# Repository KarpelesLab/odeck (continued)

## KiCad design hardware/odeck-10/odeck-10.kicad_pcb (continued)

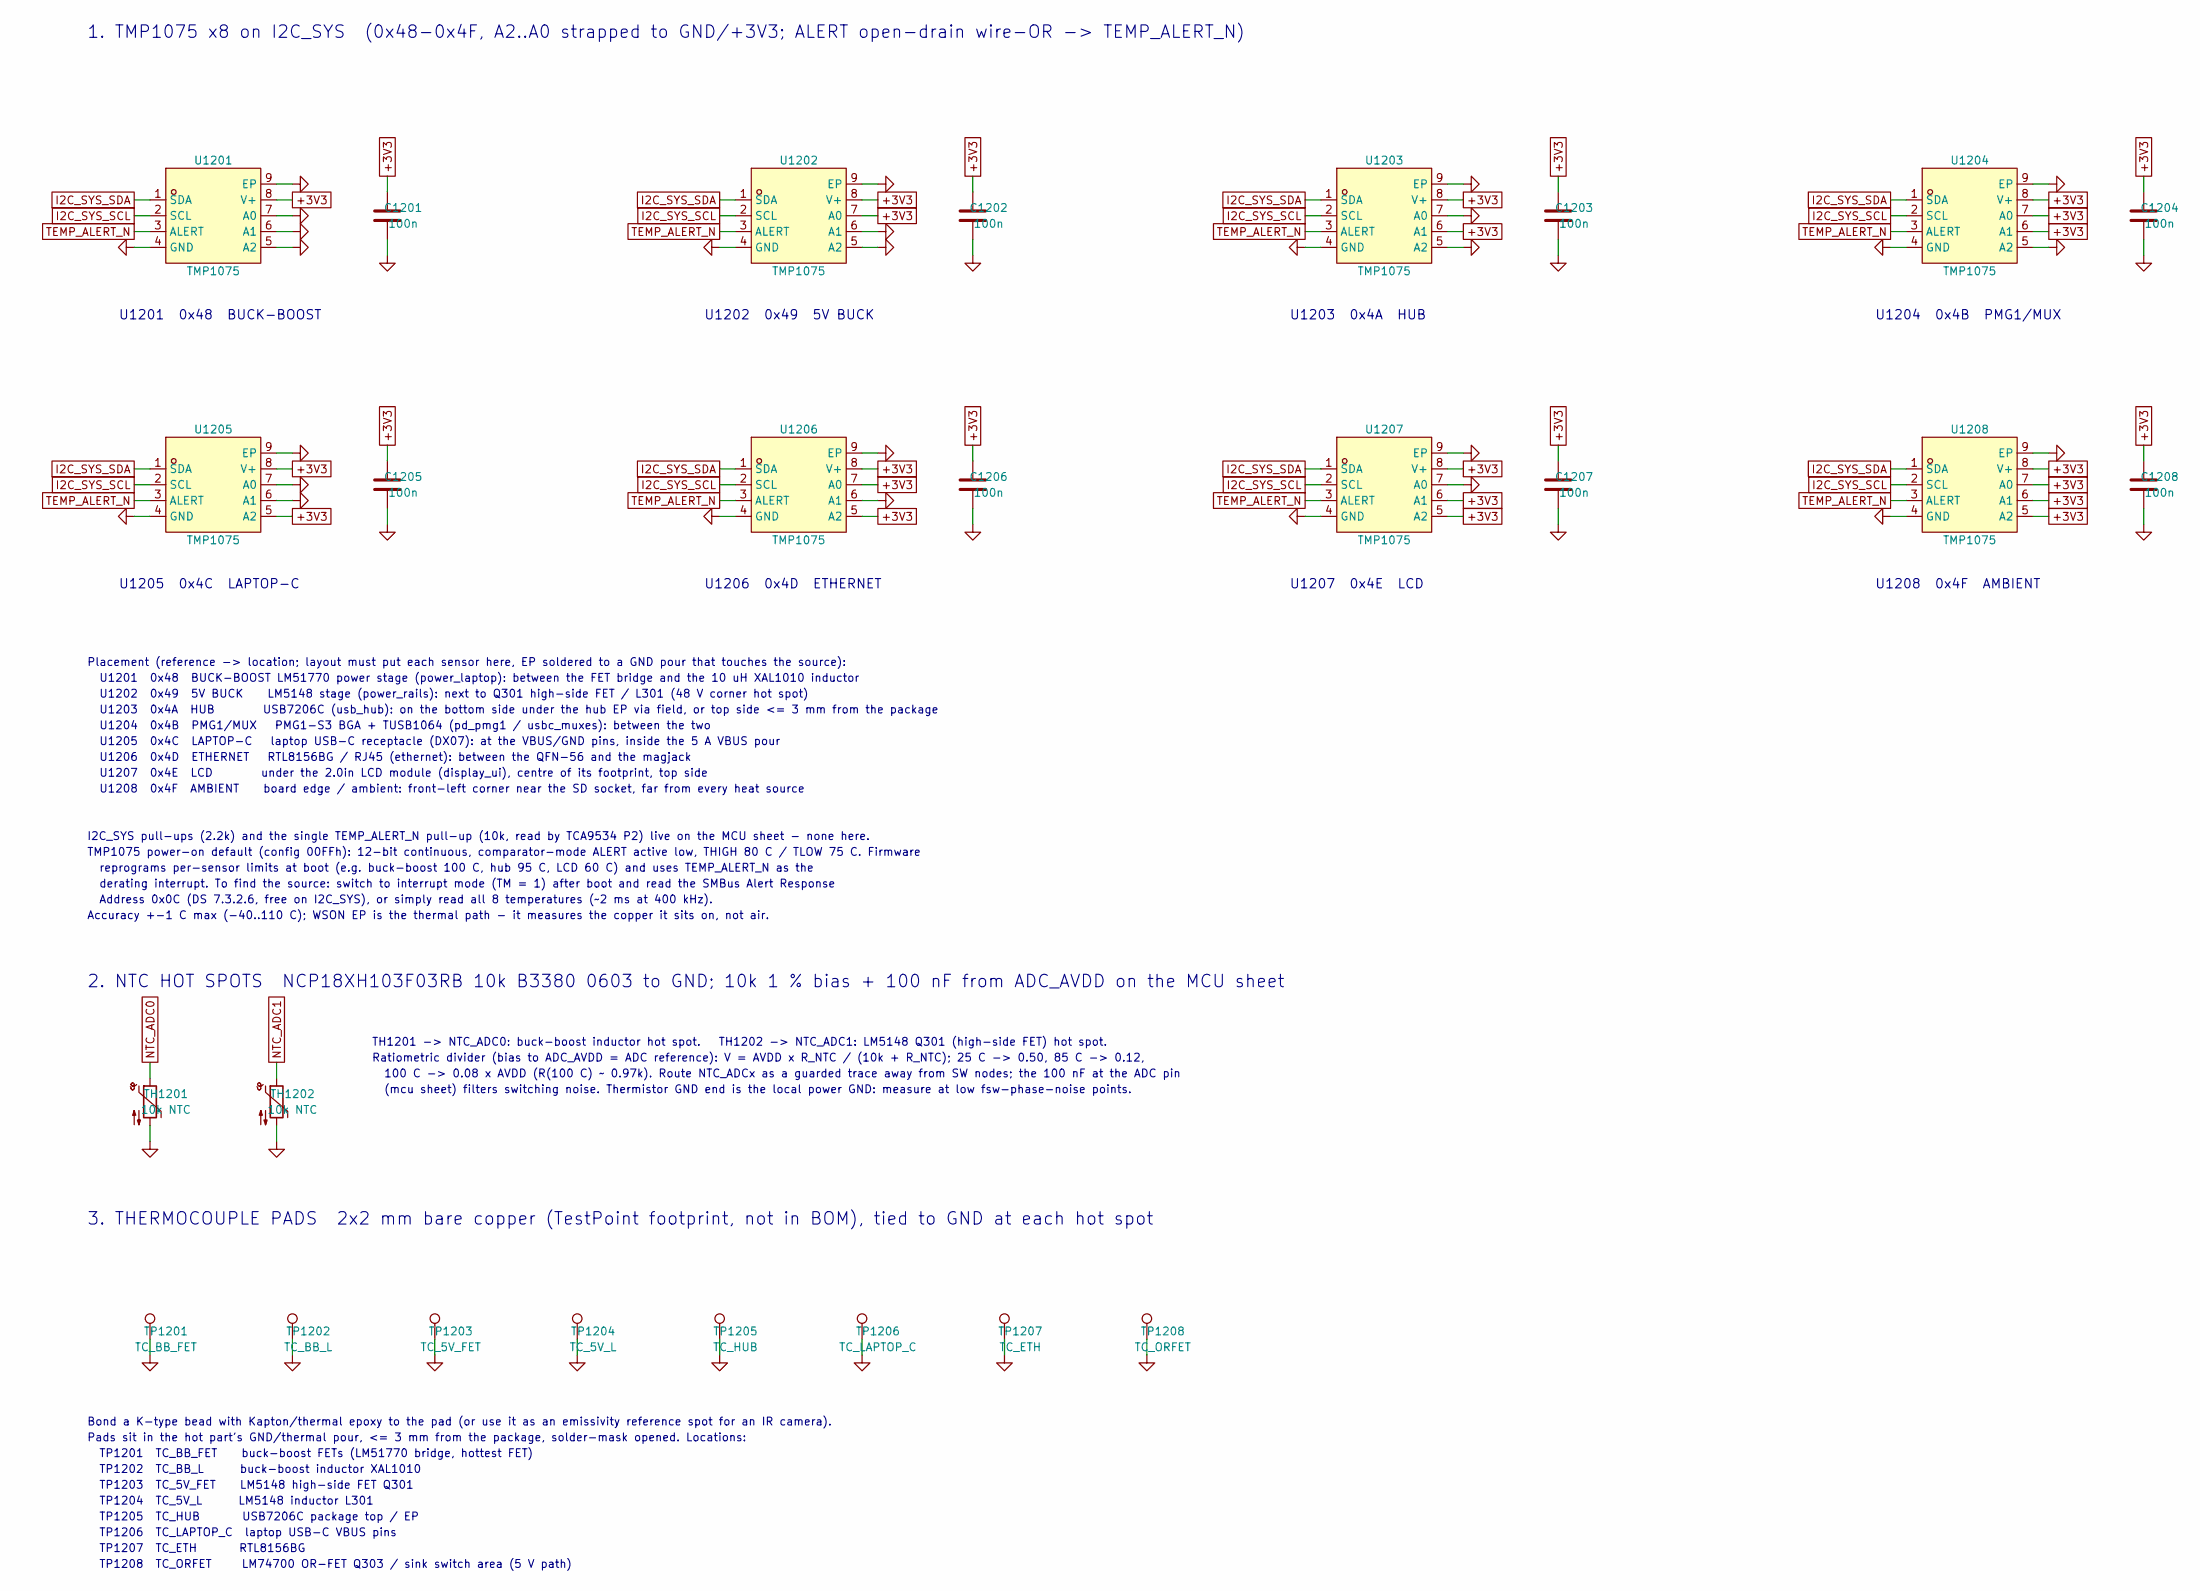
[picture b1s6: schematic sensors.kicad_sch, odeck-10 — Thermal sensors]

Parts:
C1201, C1202, C1203, C1204, C1205, C1206, C1207, C1208: 100n; C_0402_1005Metric; LCSC C1525
TH1201, TH1202: 10k NTC; R_0603_1608Metric; LCSC C13564
TP1201: TC_BB_FET; TestPoint_Pad_2.0x2.0mm
TP1202: TC_BB_L; TestPoint_Pad_2.0x2.0mm
TP1203: TC_5V_FET; TestPoint_Pad_2.0x2.0mm
TP1204: TC_5V_L; TestPoint_Pad_2.0x2.0mm
TP1205: TC_HUB; TestPoint_Pad_2.0x2.0mm
TP1206: TC_LAPTOP_C; TestPoint_Pad_2.0x2.0mm
TP1207: TC_ETH; TestPoint_Pad_2.0x2.0mm
TP1208: TC_ORFET; TestPoint_Pad_2.0x2.0mm
U1201, U1202, U1203, U1204, U1205, U1206, U1207, U1208: TMP1075; WSON-8_L2.0-W2.0-P0.50-TL-EP; MPN TMP1075DSGR; LCSC C2870250

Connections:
+3V3: C1201.1, C1202.1, C1203.1, C1204.1, C1205.1, C1206.1, C1207.1, C1208.1, U1201.8 (V+), U1202.7 (A0), U1202.8 (V+), U1203.6 (A1), U1203.8 (V+), U1204.6 (A1), U1204.7 (A0), U1204.8 (V+), U1205.5 (A2), U1205.8 (V+), U1206.5 (A2), U1206.7 (A0), U1206.8 (V+), U1207.5 (A2), U1207.6 (A1), U1207.8 (V+), U1208.5 (A2), U1208.6 (A1), U1208.7 (A0), U1208.8 (V+); also elsewhere on the board
GND: C1201.2, C1202.2, C1203.2, C1204.2, C1205.2, C1206.2, C1207.2, C1208.2, TH1201.2, TH1202.2, TP1201.1, TP1202.1, TP1203.1, TP1204.1, TP1205.1, TP1206.1, TP1207.1, TP1208.1, U1201.4 (GND), U1201.5 (A2), U1201.6 (A1), U1201.7 (A0), U1201.9 (EP), U1202.4 (GND), U1202.5 (A2), U1202.6 (A1), U1202.9 (EP), U1203.4 (GND), U1203.5 (A2), U1203.7 (A0), U1203.9 (EP), U1204.4 (GND), U1204.5 (A2), U1204.9 (EP), U1205.4 (GND), U1205.6 (A1), U1205.7 (A0), U1205.9 (EP), U1206.4 (GND), U1206.6 (A1), U1206.9 (EP), U1207.4 (GND), U1207.7 (A0), U1207.9 (EP), U1208.4 (GND), U1208.9 (EP); also elsewhere on the board
I2C_SYS_SCL: U1201.2 (SCL), U1202.2 (SCL), U1203.2 (SCL), U1204.2 (SCL), U1205.2 (SCL), U1206.2 (SCL), U1207.2 (SCL), U1208.2 (SCL); also elsewhere on the board
I2C_SYS_SDA: U1201.1 (SDA), U1202.1 (SDA), U1203.1 (SDA), U1204.1 (SDA), U1205.1 (SDA), U1206.1 (SDA), U1207.1 (SDA), U1208.1 (SDA); also elsewhere on the board
NTC_ADC0: TH1201.1; also elsewhere on the board
NTC_ADC1: TH1202.1; also elsewhere on the board
TEMP_ALERT_N: U1201.3 (ALERT), U1202.3 (ALERT), U1203.3 (ALERT), U1204.3 (ALERT), U1205.3 (ALERT), U1206.3 (ALERT), U1207.3 (ALERT), U1208.3 (ALERT); also elsewhere on the board

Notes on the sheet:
1. TMP1075 x8 on I2C_SYS (0x48-0x4F, A2..A0 strapped to GND/+3V3; ALERT open-drain wire-OR -> TEMP_ALERT_N)
U1201 0x48 BUCK-BOOST
U1202 0x49 5V BUCK
U1203 0x4A HUB
U1204 0x4B PMG1/MUX
U1205 0x4C LAPTOP-C
U1206 0x4D ETHERNET
U1207 0x4E LCD
U1208 0x4F AMBIENT
Placement (reference -> location; layout must put each sensor here, EP soldered to a GND pour that touches the source):
U1201 0x48 BUCK-BOOST LM51770 power stage (power_laptop): between the FET bridge and the 10 uH XAL1010 inductor
U1202 0x49 5V BUCK LM5148 stage (power_rails): next to Q301 high-side FET / L301 (48 V corner hot spot)
U1203 0x4A HUB USB7206C (usb_hub): on the bottom side under the hub EP via field, or top side <= 3 mm from the package
U1204 0x4B PMG1/MUX PMG1-S3 BGA + TUSB1064 (pd_pmg1 / usbc_muxes): between the two
U1205 0x4C LAPTOP-C laptop USB-C receptacle (DX07): at the VBUS/GND pins, inside the 5 A VBUS pour
U1206 0x4D ETHERNET RTL8156BG / RJ45 (ethernet): between the QFN-56 and the magjack
U1207 0x4E LCD under the 2.0in LCD module (display_ui), centre of its footprint, top side
U1208 0x4F AMBIENT board edge / ambient: front-left corner near the SD socket, far from every heat source
I2C_SYS pull-ups (2.2k) and the single TEMP_ALERT_N pull-up (10k, read by TCA9534 P2) live on the MCU sheet - none here.
TMP1075 power-on default (config 00FFh): 12-bit continuous, comparator-mode ALERT active low, THIGH 80 C / TLOW 75 C. Firmware
reprograms per-sensor limits at boot (e.g. buck-boost 100 C, hub 95 C, LCD 60 C) and uses TEMP_ALERT_N as the
derating interrupt. To find the source: switch to interrupt mode (TM = 1) after boot and read the SMBus Alert Response
Address 0x0C (DS 7.3.2.6, free on I2C_SYS), or simply read all 8 temperatures (~2 ms at 400 kHz).
Accuracy +-1 C max (-40..110 C); WSON EP is the thermal path - it measures the copper it sits on, not air.
2. NTC HOT SPOTS NCP18XH103F03RB 10k B3380 0603 to GND; 10k 1 % bias + 100 nF from ADC_AVDD on the MCU sheet
TH1201 -> NTC_ADC0: buck-boost inductor hot spot. TH1202 -> NTC_ADC1: LM5148 Q301 (high-side FET) hot spot.
Ratiometric divider (bias to ADC_AVDD = ADC reference): V = AVDD x R_NTC / (10k + R_NTC); 25 C -> 0.50, 85 C -> 0.12,
100 C -> 0.08 x AVDD (R(100 C) ~ 0.97k). Route NTC_ADCx as a guarded trace away from SW nodes; the 100 nF at the ADC pin
(mcu sheet) filters switching noise. Thermistor GND end is the local power GND: measure at low fsw-phase-noise points.
3. THERMOCOUPLE PADS 2x2 mm bare copper (TestPoint footprint, not in BOM), tied to GND at each hot spot
Bond a K-type bead with Kapton/thermal epoxy to the pad (or use it as an emissivity reference spot for an IR camera).
Pads sit in the hot part's GND/thermal pour, <= 3 mm from the package, solder-mask opened. Locations:
TP1201 TC_BB_FET buck-boost FETs (LM51770 bridge, hottest FET)
TP1202 TC_BB_L buck-boost inductor XAL1010
TP1203 TC_5V_FET LM5148 high-side FET Q301
TP1204 TC_5V_L LM5148 inductor L301
TP1205 TC_HUB USB7206C package top / EP
TP1206 TC_LAPTOP_C laptop USB-C VBUS pins
TP1207 TC_ETH RTL8156BG
TP1208 TC_ORFET LM74700 OR-FET Q303 / sink switch area (5 V path)

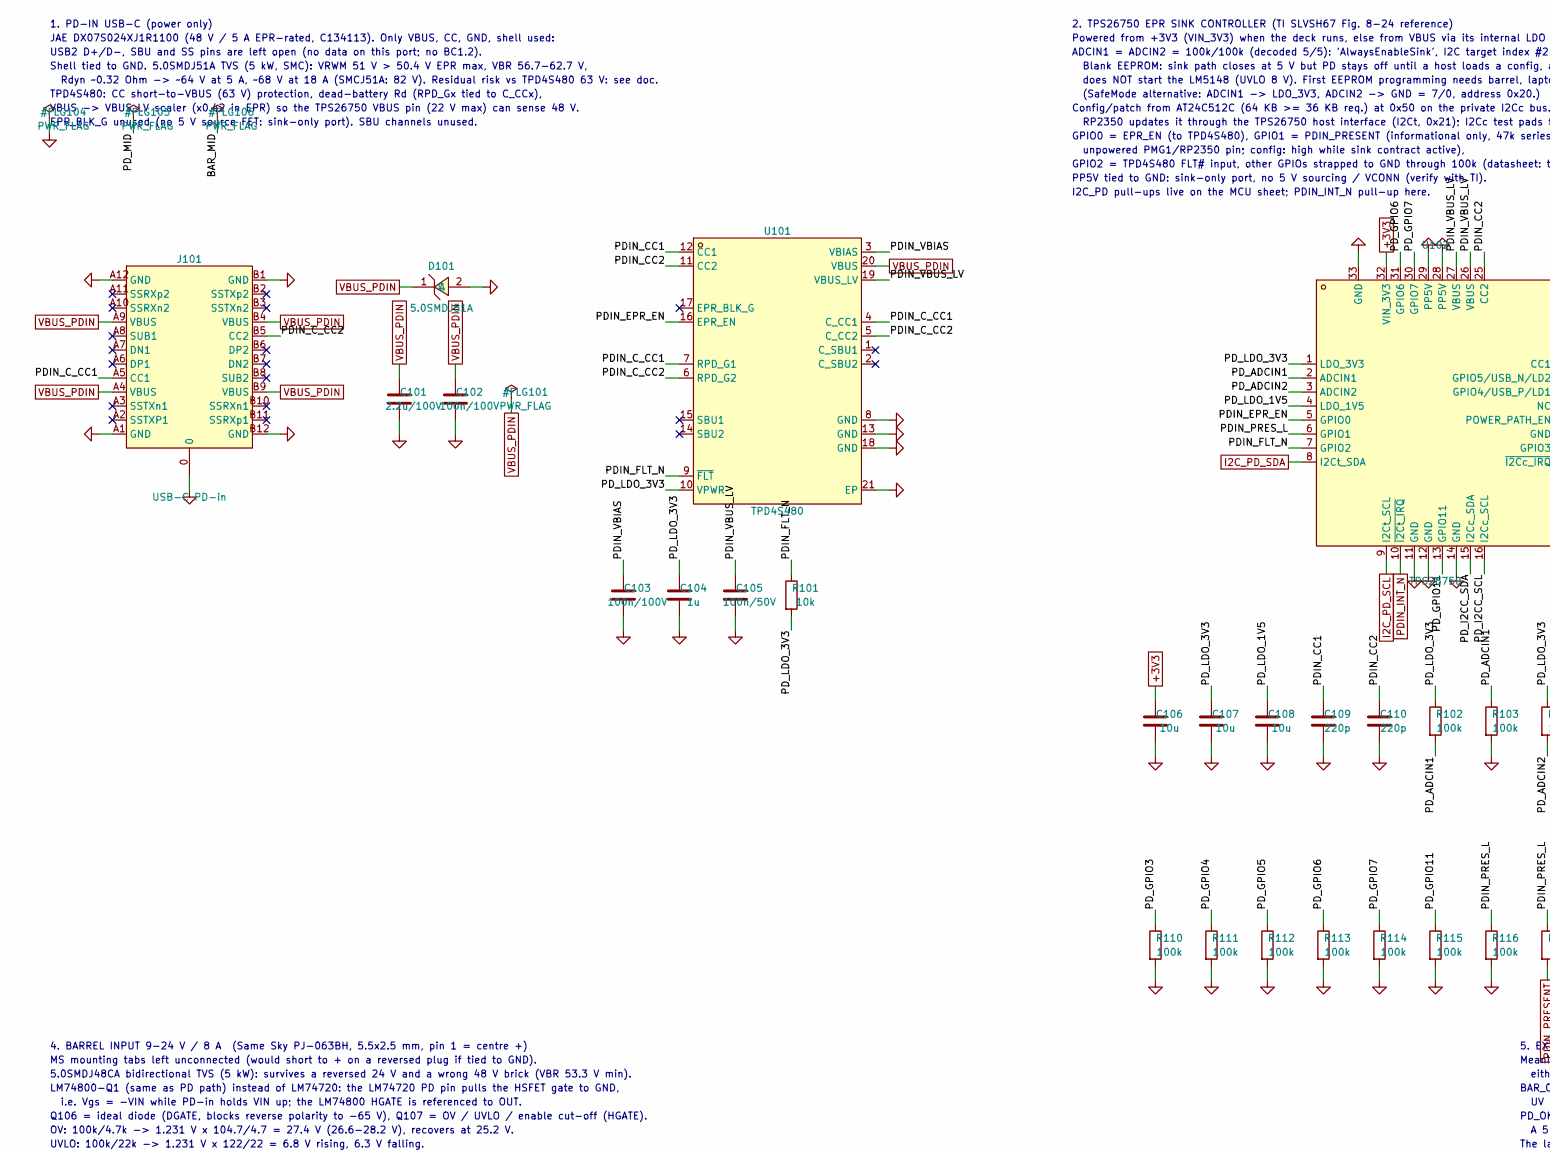
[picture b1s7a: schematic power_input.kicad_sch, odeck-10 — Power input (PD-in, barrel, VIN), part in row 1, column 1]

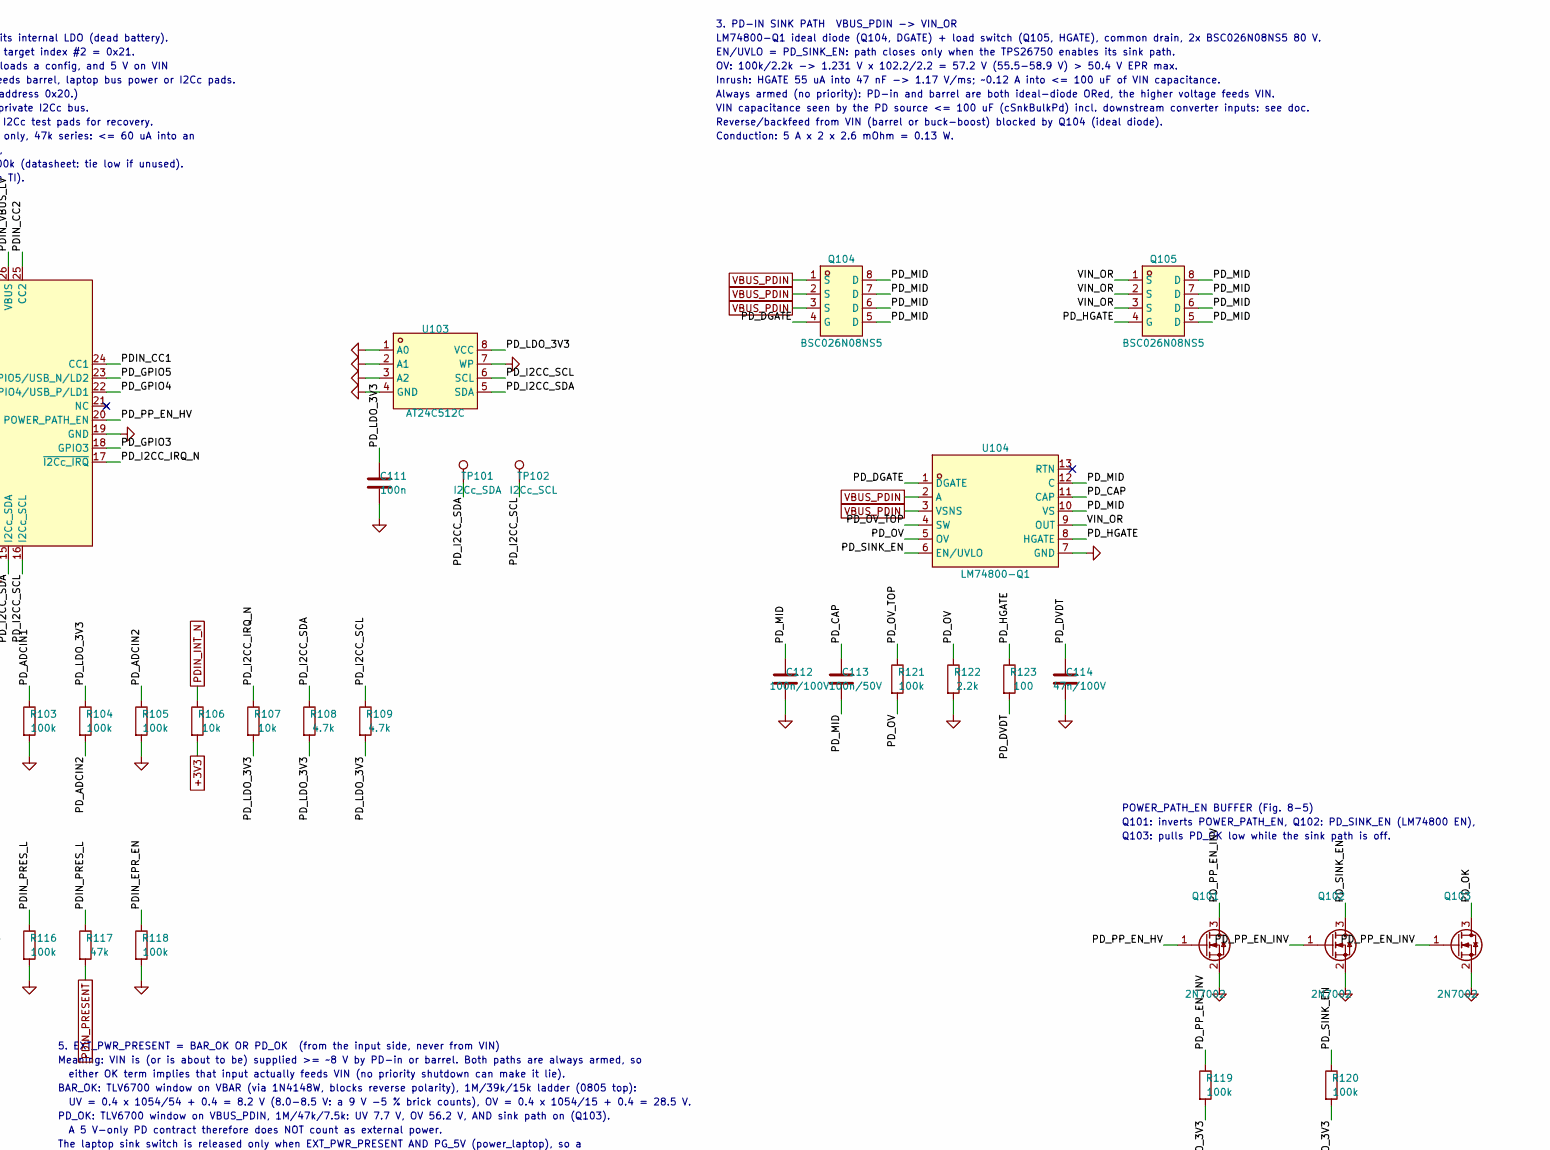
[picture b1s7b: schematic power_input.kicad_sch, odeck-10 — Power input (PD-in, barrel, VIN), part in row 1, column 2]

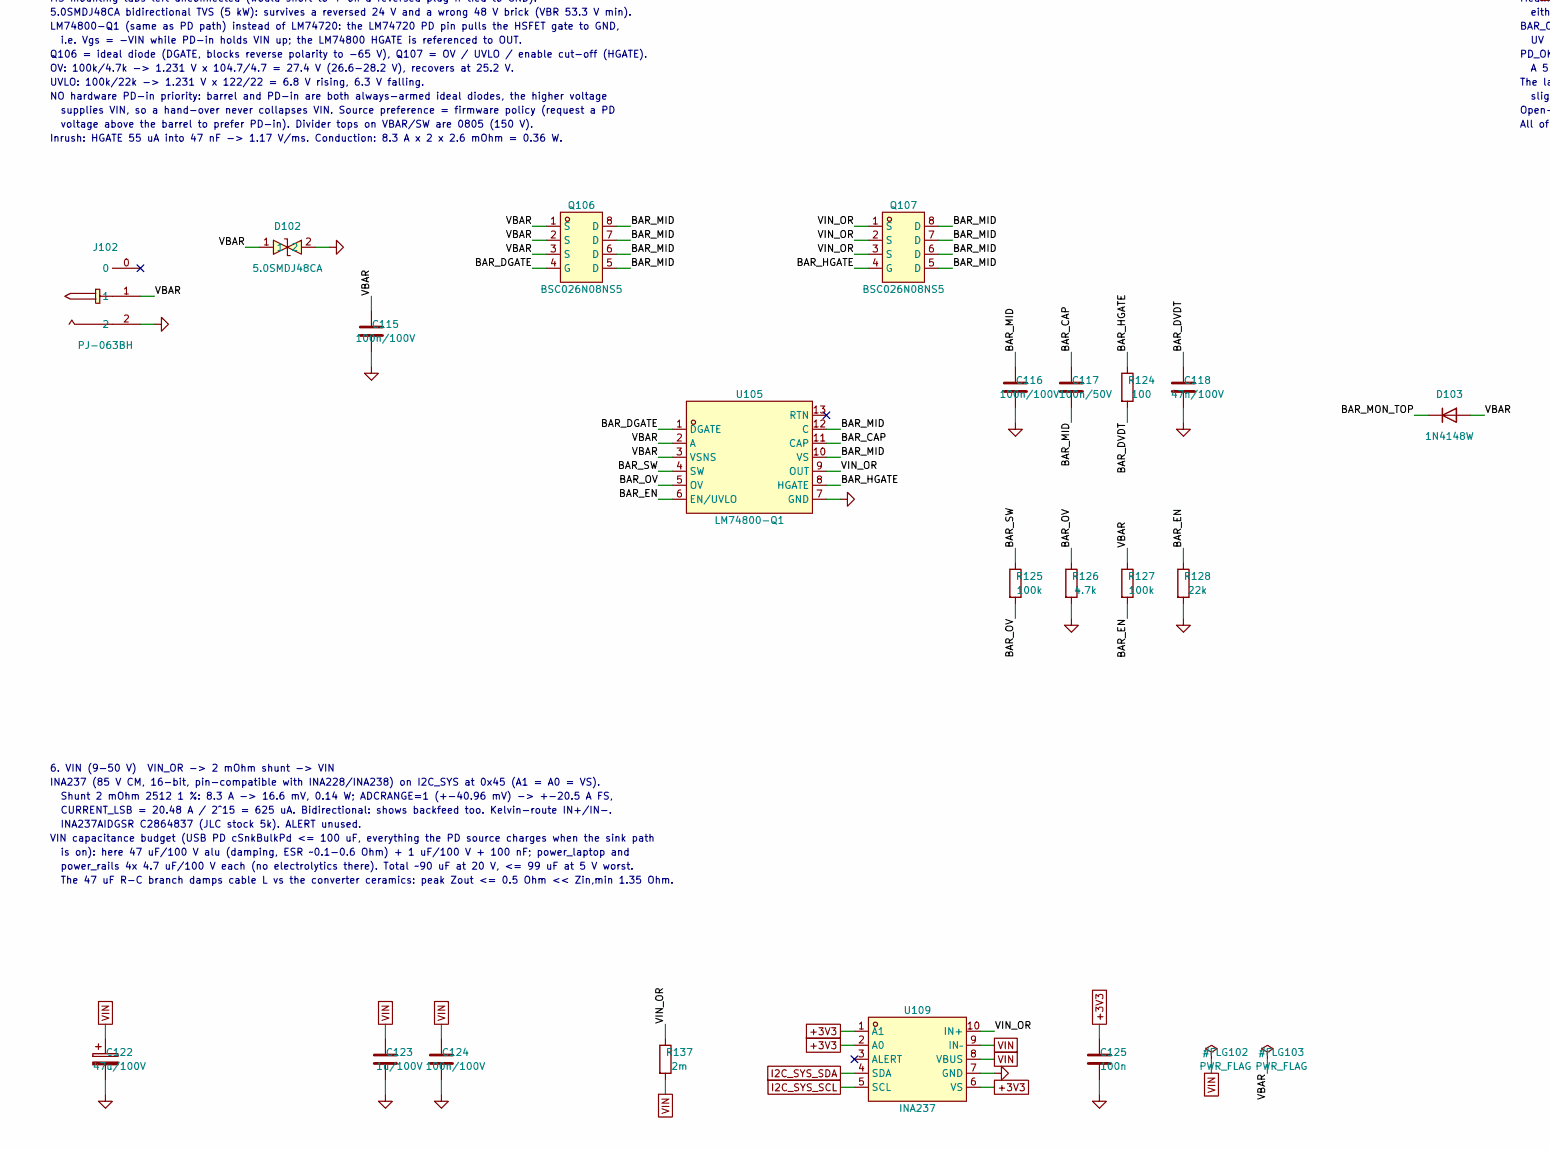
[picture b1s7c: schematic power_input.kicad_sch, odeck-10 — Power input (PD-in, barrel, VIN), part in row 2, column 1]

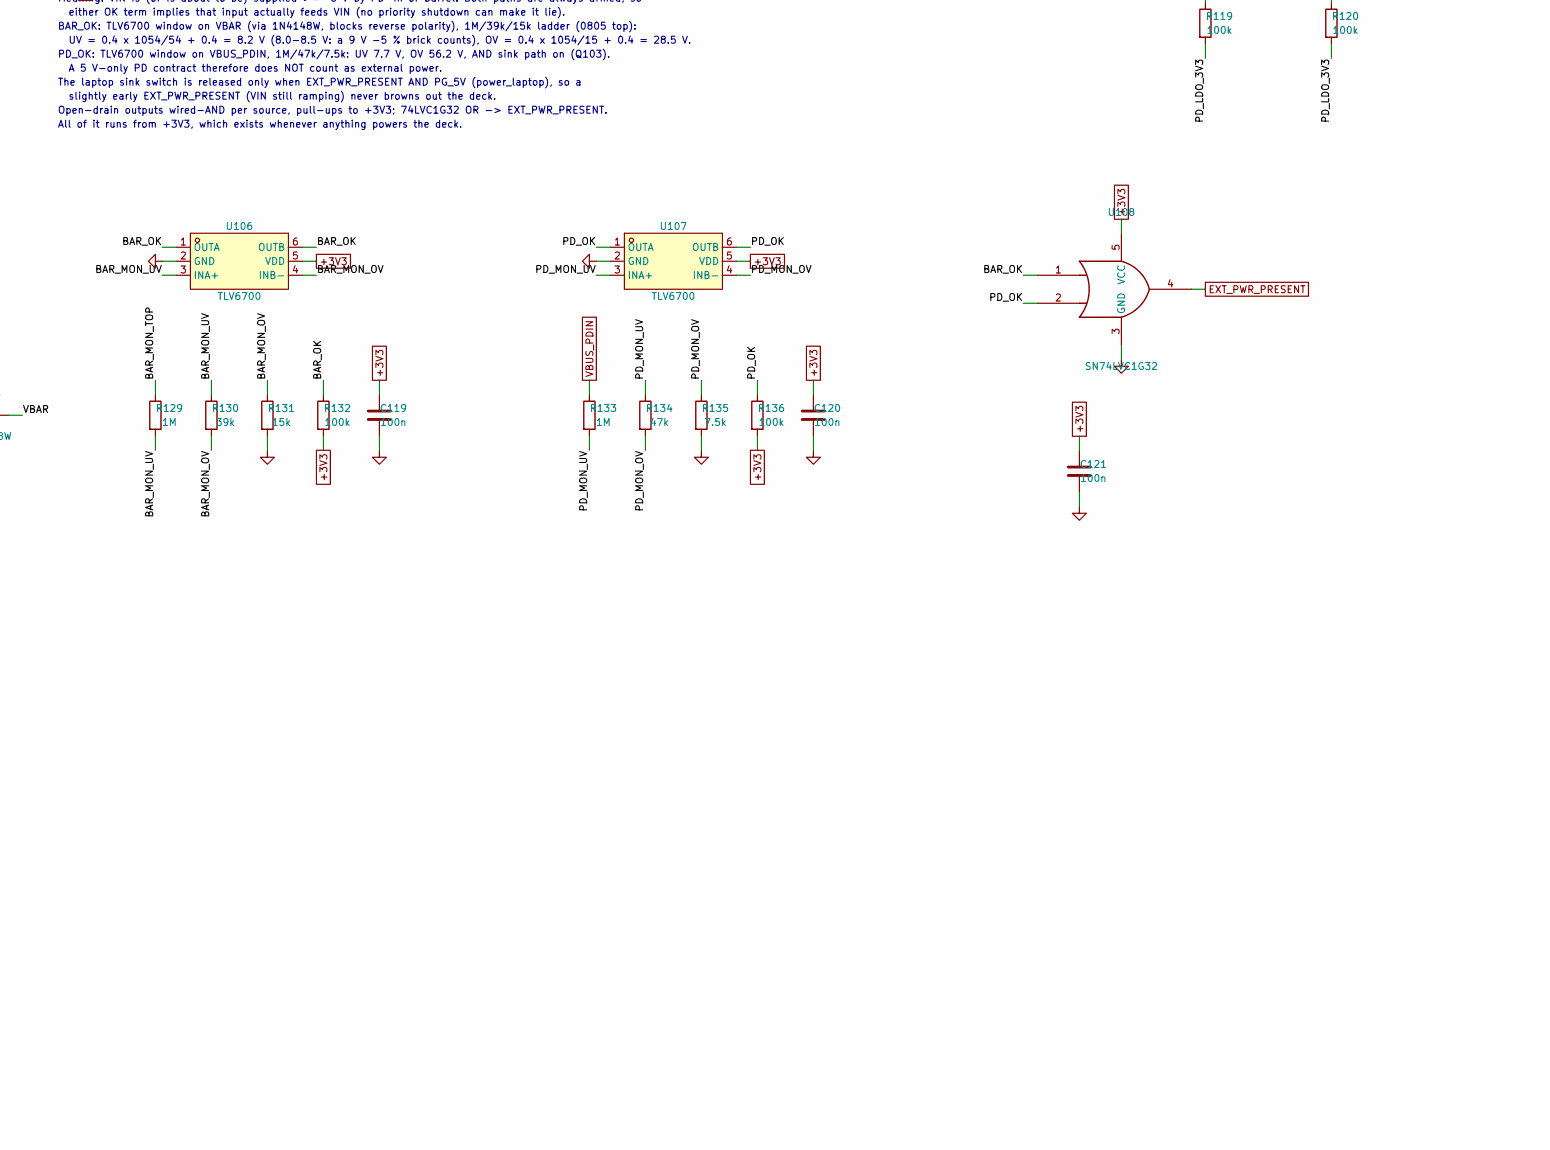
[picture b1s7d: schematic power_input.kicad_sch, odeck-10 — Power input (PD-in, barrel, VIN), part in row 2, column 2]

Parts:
C101: 2.2u/100V; C_1210_3225Metric; LCSC C153036
C102, C103, C112, C115, C116, C124: 100n/100V; C_0805_2012Metric; LCSC C28233
C104: 1u; C_0402_1005Metric; LCSC C52923
C105, C113, C117: 100n/50V; C_0603_1608Metric; LCSC C14663
C106, C107, C108: 10u; C_0603_1608Metric; LCSC C19702
C109, C110: 220p; C_0603_1608Metric; LCSC C1603
C111, C119, C120, C121, C125: 100n; C_0402_1005Metric; LCSC C1525
C114, C118: 47n/100V; C_0603_1608Metric; LCSC C576852
C122: 47u/100V; CP_Elec_10x10; LCSC C371305
C123: 1u/100V; C_0805_2012Metric; LCSC C126585
D101: 5.0SMDJ51A; SMC_L6.9-W5.9-LS7.9-RD; MPN 5.0SMDJ51A; LCSC C2990373
D102: 5.0SMDJ48CA; SMC_L6.9-W5.9-LS7.9-BI; MPN 5.0SMDJ48CA; LCSC C2649886
D103: 1N4148W; D_SOD-123; LCSC C81598
J101: USB-C PD-in; USB-C-TH_DX07S024XJ1R1100-1; MPN DX07S024XJ1R1100; LCSC C134113
J102: PJ-063BH; DC-IN_PJ-063BH; MPN PJ-063BH; LCSC C3095900
Q101, Q102, Q103: 2N7002; SOT-23; LCSC C8545
Q104, Q105, Q106, Q107: BSC026N08NS5; PG-TDSON-8_L5.0-W6.0-P1.27-BL-EP; MPN BSC026N08NS5ATMA1; LCSC C5955453
R101, R106, R107: 10k; R_0402_1005Metric; LCSC C25744
R102, R103, R104, R105, R110, R111, R112, R113, R114, R115, R116, R118, R119, R120, R132, R136: 100k; R_0402_1005Metric; LCSC C25741
R108, R109, R126: 4.7k; R_0402_1005Metric; LCSC C25900
R117, R134: 47k; R_0402_1005Metric; LCSC C25792
R121, R125, R127: 100k; R_0805_2012Metric; LCSC C149504
R122: 2.2k; R_0402_1005Metric; LCSC C25879
R123, R124: 100; R_0402_1005Metric; LCSC C25076
R128: 22k; R_0402_1005Metric; LCSC C25768
R129, R133: 1M; R_0805_2012Metric; LCSC C17514
R130: 39k; R_0603_1608Metric; LCSC C23153
R131: 15k; R_0402_1005Metric; LCSC C25756
R135: 7.5k; R_0603_1608Metric; LCSC C23234
R137: 2m; R_2512_6332Metric; MPN RLP25FEGR002; LCSC C459679
TP101: I2Cc_SDA; TestPoint_Pad_D1.0mm
TP102: I2Cc_SCL; TestPoint_Pad_D1.0mm
U101: TPD4S480; WQFN-20_L3.0-W3.0-P0.40-BL-EP1.7; MPN TPD4S480RUKR; LCSC C43131250
U102: TPS26750; QFN-32_L4.0-W4.0-P0.40-BL-EP2.8; MPN TPS26750SRSMR; LCSC C42166327
U103: AT24C512C; SOIC-8_L4.9-W3.9-P1.27-LS6.0-BL; MPN AT24C512C-SSHD-T; LCSC C12371
U104, U105: LM74800-Q1; WSON-12_L3.0-W3.0-P0.50-TL-EP-2; MPN LM74800QDRRRQ1; LCSC C3215600
U106, U107: TLV6700; TSOT-23-6_L2.9-W1.6-P0.95-LS2.8-BR; MPN TLV6700DDCR; LCSC C2868382
U108: SN74LVC1G32; SOT-23-5; LCSC C10096
U109: INA237; VSSOP-10_L3.0-W3.0-P0.50-LS4.9-BL; MPN INA237AIDGSR; LCSC C2864837

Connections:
+3V3: C106.1, C119.1, C120.1, C121.1, C125.1, R106.2, R132.2, R136.2, U102.32 (VIN_3V3), U106.5 (VDD), U107.5 (VDD), U108.5 (VCC), U109.1 (A1), U109.2 (A0), U109.6 (VS); also elsewhere on the board
/Power input/BAR_CAP: C117.1, U105.11 (CAP)
/Power input/BAR_DGATE: Q106.4 (G), U105.1 (DGATE)
/Power input/BAR_DVDT: C118.1, R124.2
/Power input/BAR_EN: R127.2, R128.1, U105.6 (EN/UVLO)
/Power input/BAR_HGATE: Q107.4 (G), R124.1, U105.8 (HGATE)
/Power input/BAR_MID: C116.1, C117.2, Q106.5 (D), Q106.6 (D), Q106.7 (D), Q106.8 (D), Q107.5 (D), Q107.6 (D), Q107.7 (D), Q107.8 (D), U105.10 (VS), U105.12 (C)
/Power input/BAR_MON_OV: R130.2, R131.1, U106.4 (INB-)
/Power input/BAR_MON_TOP: D103.1 (K), R129.1
/Power input/BAR_MON_UV: R129.2, R130.1, U106.3 (INA+)
/Power input/BAR_OK: R132.1, U106.1 (OUTA), U106.6 (OUTB), U108.1
/Power input/BAR_OV: R125.2, R126.1, U105.5 (OV)
/Power input/BAR_SW: R125.1, U105.4 (SW)
/Power input/PDIN_CC1: C109.1, U101.12 (CC1), U102.24 (CC1)
/Power input/PDIN_CC2: C110.1, U101.11 (CC2), U102.25 (CC2)
/Power input/PDIN_C_CC1: J101.A5 (CC1), U101.4 (C_CC1), U101.7 (RPD_G1)
/Power input/PDIN_C_CC2: J101.B5 (CC2), U101.5 (C_CC2), U101.6 (RPD_G2)
/Power input/PDIN_EPR_EN: R118.1, U101.16 (EPR_EN), U102.5 (GPIO0)
/Power input/PDIN_FLT_N: R101.1, U101.9 (~FLT), U102.7 (GPIO2)
/Power input/PDIN_PRES_L: R116.1, R117.1, U102.6 (GPIO1)
/Power input/PDIN_VBIAS: C103.1, U101.3 (VBIAS)
/Power input/PDIN_VBUS_LV: C105.1, U101.19 (VBUS_LV), U102.26 (VBUS), U102.27 (VBUS)
/Power input/PD_ADCIN1: R102.2, R103.1, U102.2 (ADCIN1)
/Power input/PD_ADCIN2: R104.2, R105.1, U102.3 (ADCIN2)
/Power input/PD_CAP: C113.1, U104.11 (CAP)
/Power input/PD_DGATE: Q104.4 (G), U104.1 (DGATE)
/Power input/PD_DVDT: C114.1, R123.2
/Power input/PD_GPIO3: R110.1, U102.18 (GPIO3)
/Power input/PD_GPIO4: R111.1, U102.22 (GPIO4/USB_P/LD1)
/Power input/PD_GPIO5: R112.1, U102.23 (GPIO5/USB_N/LD2)
/Power input/PD_GPIO6: R113.1, U102.31 (GPIO6)
/Power input/PD_GPIO7: R114.1, U102.30 (GPIO7)
/Power input/PD_GPIO11: R115.1, U102.13 (GPIO11)
/Power input/PD_HGATE: Q105.4 (G), R123.1, U104.8 (HGATE)
/Power input/PD_I2CC_IRQ_N: R107.1, U102.17 (~I2Cc_IRQ)
/Power input/PD_I2CC_SCL: R109.1, TP102.1, U102.16 (I2Cc_SCL), U103.6 (SCL)
/Power input/PD_I2CC_SDA: R108.1, TP101.1, U102.15 (I2Cc_SDA), U103.5 (SDA)
/Power input/PD_LDO_1V5: C108.1, U102.4 (LDO_1V5)
/Power input/PD_LDO_3V3: C104.1, C107.1, C111.1, R101.2, R102.1, R104.1, R107.2, R108.2, R109.2, R119.2, R120.2, U101.10 (VPWR), U102.1 (LDO_3V3), U103.8 (VCC)
/Power input/PD_MID: C112.1, C113.2, Q104.5 (D), Q104.6 (D), Q104.7 (D), Q104.8 (D), Q105.5 (D), Q105.6 (D), Q105.7 (D), Q105.8 (D), U104.10 (VS), U104.12 (C)
/Power input/PD_MON_OV: R134.2, R135.1, U107.4 (INB-)
/Power input/PD_MON_UV: R133.2, R134.1, U107.3 (INA+)
/Power input/PD_OK: Q103.3 (D), R136.1, U107.1 (OUTA), U107.6 (OUTB), U108.2
/Power input/PD_OV: R121.2, R122.1, U104.5 (OV)
/Power input/PD_OV_TOP: R121.1, U104.4 (SW)
/Power input/PD_PP_EN_HV: Q101.1 (G), U102.20 (POWER_PATH_EN)
/Power input/PD_PP_EN_INV: Q101.3 (D), Q102.1 (G), Q103.1 (G), R119.1
/Power input/PD_SINK_EN: Q102.3 (D), R120.1, U104.6 (EN/UVLO)
/Power input/VBAR: C115.1, D102.1, D103.2 (A), J102.1, Q106.1 (S), Q106.2 (S), Q106.3 (S), R127.1, U105.2 (A), U105.3 (VSNS)
/Power input/VIN_OR: Q105.1 (S), Q105.2 (S), Q105.3 (S), Q107.1 (S), Q107.2 (S), Q107.3 (S), R137.1, U104.9 (OUT), U105.9 (OUT), U109.10 (IN+)
EXT_PWR_PRESENT: U108.4; also elsewhere on the board
GND: C101.2, C102.2, C103.2, C104.2, C105.2, C106.2, C107.2, C108.2, C109.2, C110.2, C111.2, C112.2, C114.2, C115.2, C116.2, C118.2, C119.2, C120.2, C121.2, C122.2, C123.2, C124.2, C125.2, D101.2 (A), D102.2, J101.0, J101.A1 (GND), J101.A12 (GND), J101.B1 (GND), J101.B12 (GND), J102.2, Q101.2 (S), Q102.2 (S), Q103.2 (S), R103.2, R105.2, R110.2, R111.2, R112.2, R113.2, R114.2, R115.2, R116.2, R118.2, R122.2, R126.2, R128.2, R131.2, R135.2, U101.8 (GND), U101.13 (GND), U101.18 (GND), U101.21 (EP), U102.11 (GND), U102.12 (GND), U102.14 (GND), U102.19 (GND), U102.28 (PP5V), U102.29 (PP5V), U102.33 (GND), U103.1 (A0), U103.2 (A1), U103.3 (A2), U103.4 (GND), U103.7 (WP), U104.7 (GND), U105.7 (GND), U106.2 (GND), U107.2 (GND), U108.3 (GND), U109.7 (GND); also elsewhere on the board
I2C_PD_SCL: U102.9 (I2Ct_SCL); also elsewhere on the board
I2C_PD_SDA: U102.8 (I2Ct_SDA); also elsewhere on the board
I2C_SYS_SCL: U109.5 (SCL); also elsewhere on the board
I2C_SYS_SDA: U109.4 (SDA); also elsewhere on the board
PDIN_INT_N: R106.1, U102.10 (~I2Ct_IRQ); also elsewhere on the board
PDIN_PRESENT: R117.2; also elsewhere on the board
VBUS_PDIN: C101.1, C102.1, D101.1 (C), J101.A4 (VBUS), J101.A9 (VBUS), J101.B4 (VBUS), J101.B9 (VBUS), Q104.1 (S), Q104.2 (S), Q104.3 (S), R133.1, U101.20 (VBUS), U104.2 (A), U104.3 (VSNS)
VIN: C122.1, C123.1, C124.1, R137.2, U109.8 (VBUS), U109.9 (IN–); also elsewhere on the board

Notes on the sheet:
1. PD-IN USB-C (power only)
JAE DX07S024XJ1R1100 (48 V / 5 A EPR-rated, C134113). Only VBUS, CC, GND, shell used:
USB2 D+/D-, SBU and SS pins are left open (no data on this port; no BC1.2).
Shell tied to GND. 5.0SMDJ51A TVS (5 kW, SMC): VRWM 51 V > 50.4 V EPR max, VBR 56.7-62.7 V,
Rdyn ~0.32 Ohm -> ~64 V at 5 A, ~68 V at 18 A (SMCJ51A: 82 V). Residual risk vs TPD4S480 63 V: see doc.
TPD4S480: CC short-to-VBUS (63 V) protection, dead-battery Rd (RPD_Gx tied to C_CCx),
VBUS -> VBUS_LV scaler (x0.42 in EPR) so the TPS26750 VBUS pin (22 V max) can sense 48 V.
EPR_BLK_G unused (no 5 V source FET: sink-only port). SBU channels unused.
2. TPS26750 EPR SINK CONTROLLER (TI SLVSH67 Fig. 8-24 reference)
Powered from +3V3 (VIN_3V3) when the deck runs, else from VBUS via its internal LDO (dead battery).
ADCIN1 = ADCIN2 = 100k/100k (decoded 5/5): 'AlwaysEnableSink', I2C target index #2 = 0x21.
Blank EEPROM: sink path closes at 5 V but PD stays off until a host loads a config, and 5 V on VIN
does NOT start the LM5148 (UVLO 8 V). First EEPROM programming needs barrel, laptop bus power or I2Cc pads.
(SafeMode alternative: ADCIN1 -> LDO_3V3, ADCIN2 -> GND = 7/0, address 0x20.)
Config/patch from AT24C512C (64 KB >= 36 KB req.) at 0x50 on the private I2Cc bus.
RP2350 updates it through the TPS26750 host interface (I2Ct, 0x21); I2Cc test pads for recovery.
GPIO0 = EPR_EN (to TPD4S480), GPIO1 = PDIN_PRESENT (informational only, 47k series: <= 60 uA into an
unpowered PMG1/RP2350 pin; config: high while sink contract active),
GPIO2 = TPD4S480 FLT# input, other GPIOs strapped to GND through 100k (datasheet: tie low if unused).
PP5V tied to GND: sink-only port, no 5 V sourcing / VCONN (verify with TI).
I2C_PD pull-ups live on the MCU sheet; PDIN_INT_N pull-up here.
POWER_PATH_EN BUFFER (Fig. 8-5)
Q101: inverts POWER_PATH_EN, Q102: PD_SINK_EN (LM74800 EN),
Q103: pulls PD_OK low while the sink path is off.
3. PD-IN SINK PATH VBUS_PDIN -> VIN_OR
LM74800-Q1 ideal diode (Q104, DGATE) + load switch (Q105, HGATE), common drain, 2x BSC026N08NS5 80 V.
EN/UVLO = PD_SINK_EN: path closes only when the TPS26750 enables its sink path.
OV: 100k/2.2k -> 1.231 V x 102.2/2.2 = 57.2 V (55.5-58.9 V) > 50.4 V EPR max.
Inrush: HGATE 55 uA into 47 nF -> 1.17 V/ms; ~0.12 A into <= 100 uF of VIN capacitance.
Always armed (no priority): PD-in and barrel are both ideal-diode ORed, the higher voltage feeds VIN.
VIN capacitance seen by the PD source <= 100 uF (cSnkBulkPd) incl. downstream converter inputs: see doc.
Reverse/backfeed from VIN (barrel or buck-boost) blocked by Q104 (ideal diode).
Conduction: 5 A x 2 x 2.6 mOhm = 0.13 W.
4. BARREL INPUT 9-24 V / 8 A (Same Sky PJ-063BH, 5.5x2.5 mm, pin 1 = centre +)
MS mounting tabs left unconnected (would short to + on a reversed plug if tied to GND).
5.0SMDJ48CA bidirectional TVS (5 kW): survives a reversed 24 V and a wrong 48 V brick (VBR 53.3 V min).
LM74800-Q1 (same as PD path) instead of LM74720: the LM74720 PD pin pulls the HSFET gate to GND,
i.e. Vgs = -VIN while PD-in holds VIN up; the LM74800 HGATE is referenced to OUT.
Q106 = ideal diode (DGATE, blocks reverse polarity to -65 V), Q107 = OV / UVLO / enable cut-off (HGATE).
OV: 100k/4.7k -> 1.231 V x 104.7/4.7 = 27.4 V (26.6-28.2 V), recovers at 25.2 V.
